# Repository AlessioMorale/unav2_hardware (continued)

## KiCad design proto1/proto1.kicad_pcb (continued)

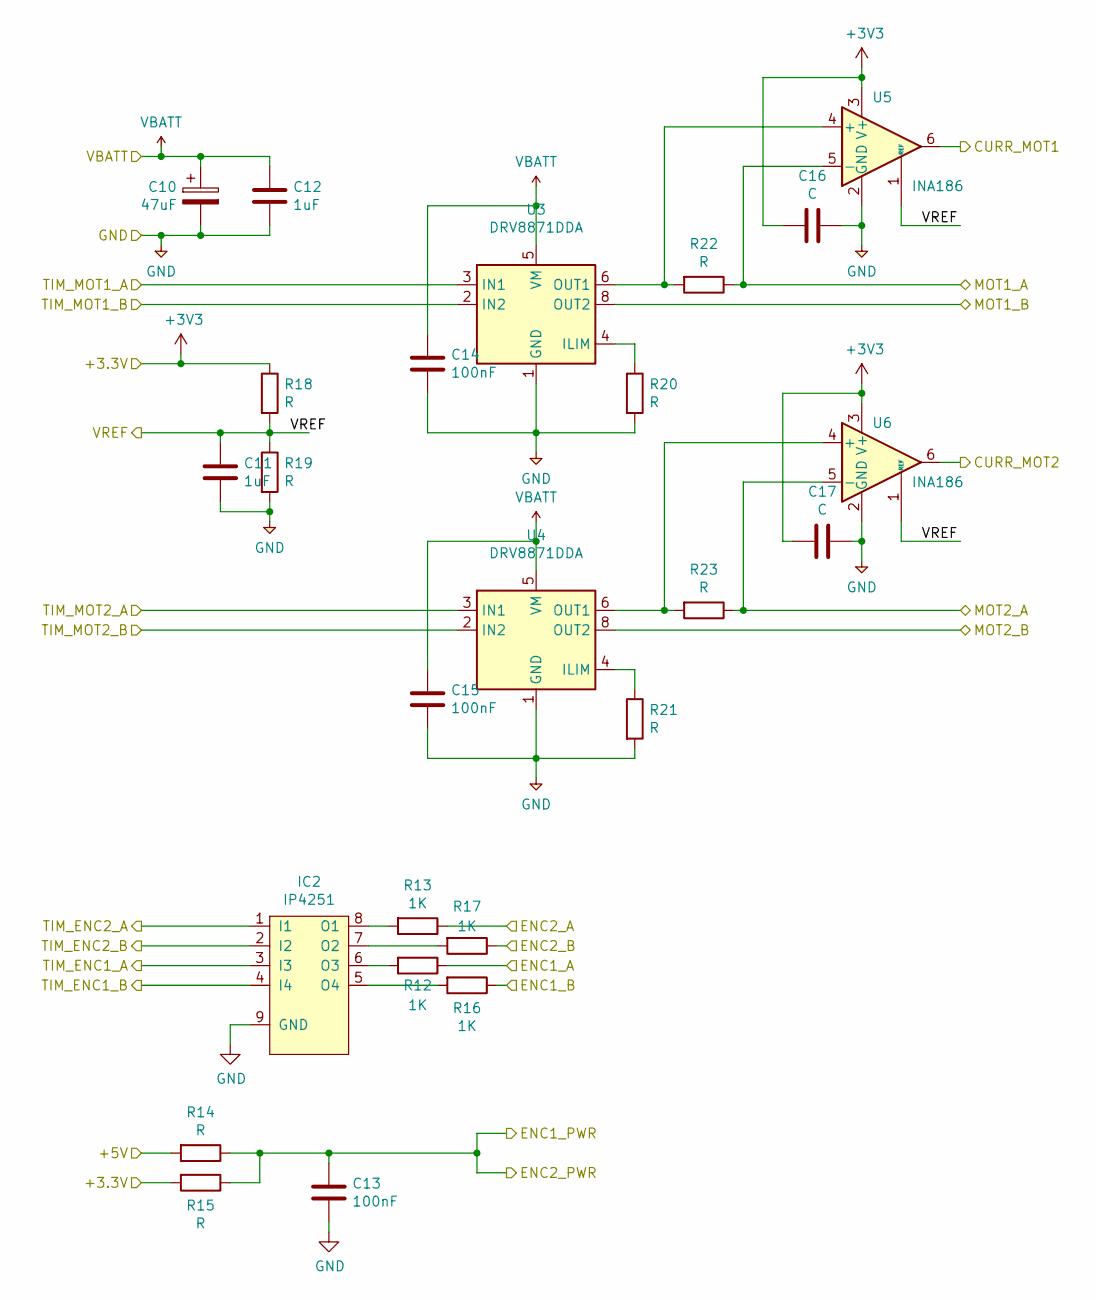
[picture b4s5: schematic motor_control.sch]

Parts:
C10: 47uF; CP_Elec_6.3x5.8
C11: 1uF; C_0402_1005Metric
C12: 1uF; C_0805_2012Metric
C13, C14, C15: 100nF; C_0603_1608Metric
C16, C17: C; C_0402_1005Metric
IC2: IP4251; HUSON8; Digikey 1727-5678-1-ND
R12, R13, R16, R17: 1K; R_0402_1005Metric
R14, R15, R18, R19, R20, R21: R; R_0402_1005Metric
R22, R23: R; R_0805_2012Metric
U3, U4: DRV8871DDA; Texas_HTSOP-8-1EP_3.9x4.9mm_P1.27mm_EP2.95x4.9mm_Mask2.4x3.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
U5, U6: INA186; SOT-23-6

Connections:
+3V3: C16.2, C17.2, R15.2, R18.1, U5.3 (V+), U6.3 (V+); also elsewhere on the board
+5V: R14.2; also elsewhere on the board
+BATT: C10.1, C12.1, C14.1, C15.1, U3.5 (VM), U4.5 (VM); also elsewhere on the board
/Motor control/ENC1_A: R12.1; also elsewhere on the board
/Motor control/ENC1_B: R16.1; also elsewhere on the board
/Motor control/ENC1_PWR: C13.1, R14.1, R15.1; also elsewhere on the board
/Motor control/ENC2_A: R13.1; also elsewhere on the board
/Motor control/ENC2_B: R17.1; also elsewhere on the board
/Motor control/MOT1_A: R22.1, U5.5 (-); also elsewhere on the board
/Motor control/MOT1_B: U3.8 (OUT2); also elsewhere on the board
/Motor control/MOT2_A: R23.1, U6.5 (-); also elsewhere on the board
/Motor control/MOT2_B: U4.8 (OUT2); also elsewhere on the board
/PC0: U5.6; also elsewhere on the board
/PC1: U6.6; also elsewhere on the board
/PC3: C11.1, R18.2, R19.1, U5.1 (REF), U6.1 (REF); also elsewhere on the board
/PC6: IC2.3 (I3); also elsewhere on the board
/PC7: IC2.4 (I4); also elsewhere on the board
/PD12: IC2.1 (I1); also elsewhere on the board
/PD13: IC2.2 (I2); also elsewhere on the board
/PE8: U3.2 (IN2); also elsewhere on the board
/PE9: U3.3 (IN1); also elsewhere on the board
/PE10: U4.2 (IN2); also elsewhere on the board
/PE11: U4.3 (IN1); also elsewhere on the board
GND: C10.2, C11.2, C12.2, C13.2, C14.2, C15.2, C16.1, C17.1, IC2.9 (GND), R19.2, R20.2, R21.2, U3.1 (GND), U3.7 (GND), U3.9 (GND), U4.1 (GND), U4.7 (GND), U4.9 (GND), U5.2 (GND), U6.2 (GND); also elsewhere on the board
unnamed: IC2.5 (O4), R16.2
unnamed: IC2.6 (O3), R12.2
unnamed: IC2.7 (O2), R17.2
unnamed: IC2.8 (O1), R13.2
unnamed: R20.1, U3.4 (ILIM)
unnamed: R21.1, U4.4 (ILIM)
unnamed: R22.2, U3.6 (OUT1), U5.4 (+)
unnamed: R23.2, U4.6 (OUT1), U6.4 (+)

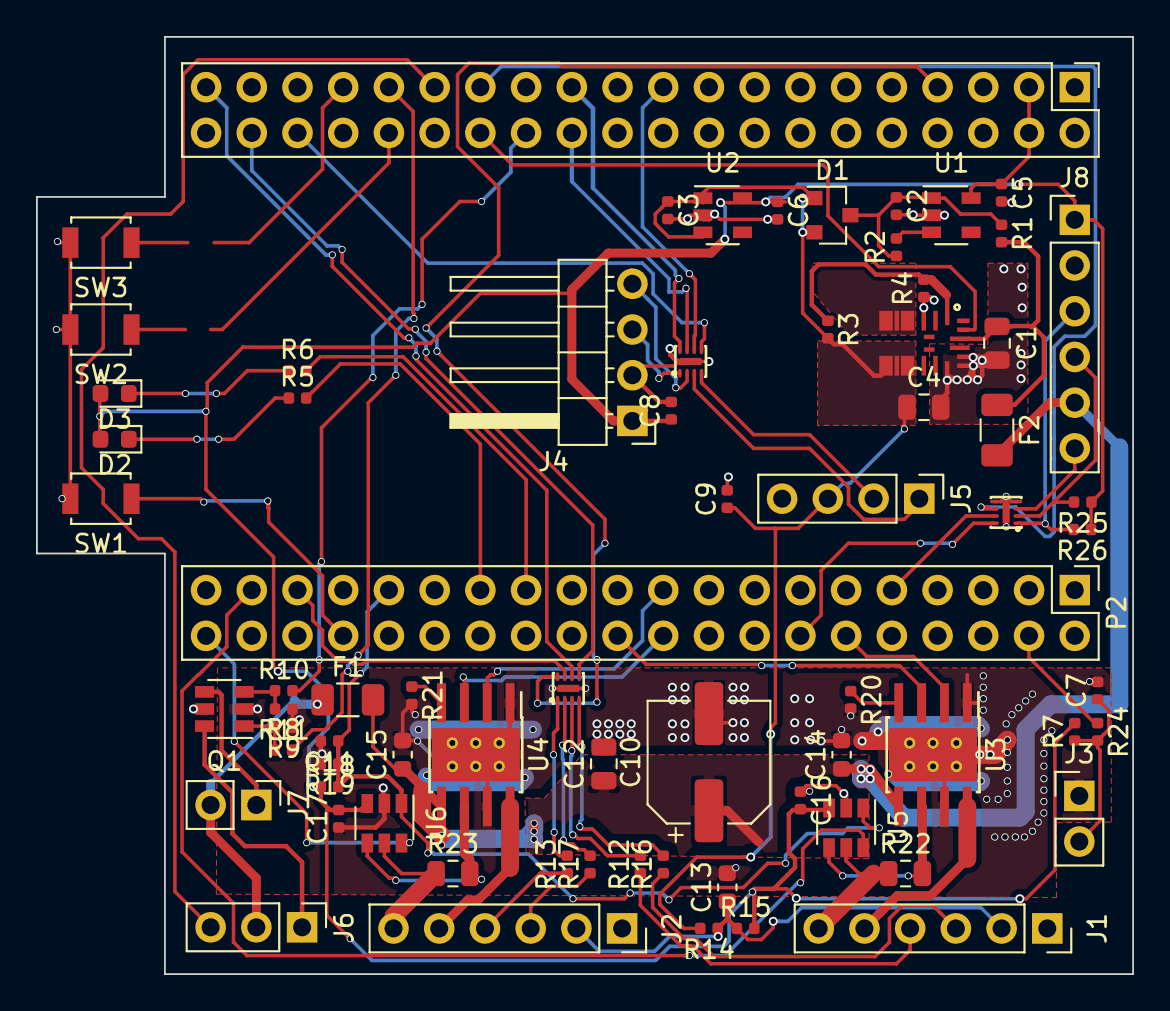
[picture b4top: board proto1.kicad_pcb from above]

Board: 2 copper layers, 60.9 x 52.1 mm, 72 parts (0 on the bottom side), 71 nets.

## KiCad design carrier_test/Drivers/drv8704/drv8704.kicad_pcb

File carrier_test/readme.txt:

Link to docs for the F4 board used:

doc
http://wiki.stm32duino.com/index.php?title=STM32F407

schematic
http://wiki.stm32duino.com/images/5/5c/STM32_F4VE_SCHEMATIC.PDF

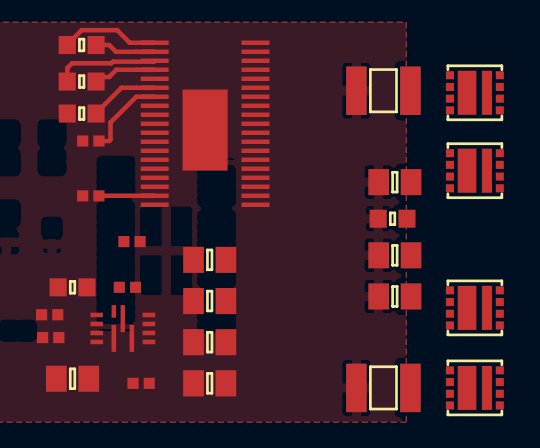
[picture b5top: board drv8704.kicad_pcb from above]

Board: 2 copper layers, 28 parts (0 on the bottom side), 29 nets.

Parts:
C1, C6, C7: 0.1μF; 0603
C2, C3, C5, C9, C13, C14, C15, C16: 22UF; 0805
C4: 0.1UF; 0402
C8, C10: 1UF; 0603
IC1: DRV8704; HTSSOP-38
IC2: MP8759; QFN-12_MPS_NB679
Q1, Q2, Q3, Q4: SiZ340DT; PowerPair-3x3
R1: 10K; 0402
R2, R3: 0.001; 1210
R4: 3.3; 0402
R5, R6: NC; 0402
R7: 41.2K; 0402
R8: 5.6K; 0402

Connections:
/Driver/A1: IC1.37, Q2.S1D2
/Driver/A2: IC1.30, Q4.S1D2
/Driver/B1: IC1.28, Q1.S1D2
/Driver/B2: IC1.21, Q3.S1D2
/Driver/BIN2: IC1.12, IC1.13
/Driver/FAULTn: IC1.18, R1.1
/Driver/VMOT: C1.1, C2.1, C3.1, C5.1, C8.2, IC1.4, Q1.D1, Q2.D1, Q3.D1, Q4.D1
/Power/VIN: C9.1, IC2.1
/Power/Vout: C13.2, C14.2, C15.2, C16.2, IC2.5, R7.1
GND: C1.2, C2.2, C3.2, C4.1, C5.2, C6.2, C10.2, C13.1, C14.1, C15.1, C16.1, IC1.5, IC1.19, IC1.24, IC1.33, IC1.38, IC1.39, IC2.2, IC2.10, R2.2, R3.2, R8.2
unnamed: C4.2, IC1.7
unnamed: C6.1, IC1.6
unnamed: C7.1, IC1.1
unnamed: C7.2, IC1.2
unnamed: C8.1, IC1.3
unnamed: C10.1, IC2.9
unnamed: IC2.7, R5.1, R5.2, R6.1
unnamed: IC1.22, Q3.G1
unnamed: IC1.23, Q3.G2
unnamed: IC1.25, Q1.S2, Q3.S2, R3.1
unnamed: IC1.26, Q1.G2
unnamed: IC1.27, Q1.G1
unnamed: IC1.31, Q4.G1
unnamed: IC1.32, Q4.G2
unnamed: IC1.34, Q2.S2, Q4.S2, R2.1
unnamed: IC1.35, Q2.G2
unnamed: IC1.36, Q2.G1
unnamed: IC2.8, R4.1
unnamed: IC2.11, R6.2, R7.2, R8.1

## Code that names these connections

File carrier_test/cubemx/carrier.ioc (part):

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Mcu.Name=STM32F407V(E-G)Tx
Mcu.Package=LQFP100
Mcu.UserName=STM32F407VETx
PA0-WKUP.GPIOParameters=GPIO_Label
PA0-WKUP.GPIO_Label=I_KEY_UP
PA0-WKUP.Mode=SYS_WakeUp0
PA0-WKUP.Signal=SYS_WKUP
PA1.GPIOParameters=GPIO_Label
PA1.GPIO_Label=TIM_ENC3_B
PA1.Signal=S_TIM2_CH2
PA10.Mode=Asynchronous
PA10.Signal=USART1_RX
PA11.Mode=Device_Only
PA11.Signal=USB_OTG_FS_DM
PA12.Mode=Device_Only
PA12.Signal=USB_OTG_FS_DP
PA13.Mode=Serial_Wire
PA13.Signal=SYS_JTMS-SWDIO
PA14.Mode=Serial_Wire
PA14.Signal=SYS_JTCK-SWCLK
PA2.GPIOParameters=GPIO_Label
PA2.GPIO_Label=ADC_TEMP
PA2.Signal=ADCx_IN2
PA3.Signal=ADCx_IN3
PA5.GPIOParameters=GPIO_Label
PA5.GPIO_Label=TIM_ENC3_A
PA5.Signal=S_TIM2_CH1_ETR
PA6.GPIOParameters=GPIO_Label
PA6.GPIO_Label=O_LED1
PA6.Signal=GPIO_Output
PA7.GPIOParameters=GPIO_Label
PA7.GPIO_Label=O_LED2
PA7.Signal=GPIO_Output
PA9.Mode=Asynchronous
PA9.Signal=USART1_TX
PB0.GPIOParameters=GPIO_Label
PB0.GPIO_Label=O_FLASH_CS
PB0.Signal=GPIO_Output
PB1.GPIOParameters=GPIO_Label
PB1.GPIO_Label=O_SPI_CS2
PB1.Signal=GPIO_Output
PB10.Mode=Asynchronous
PB10.Signal=USART3_TX
PB11.Mode=Asynchronous
PB11.Signal=USART3_RX
PB12.GPIOParameters=GPIO_Label
PB12.GPIO_Label=I_MOT_FAULT1
PB12.Signal=GPXTI12
PB13.GPIOParameters=GPIO_Label
PB13.GPIO_Label=I_MOT_FAULT2
PB13.Signal=GPIO_Input
PB14.GPIOParameters=GPIO_Label
PB14.GPIO_Label=I_MOT_FAULT3
PB14.Signal=GPIO_Input
PB15.GPIOParameters=GPIO_Label
PB15.GPIO_Label=TIM_AUX2_PWM
PB15.Signal=S_TIM12_CH2
PB3.Mode=Full_Duplex_Master
PB3.Signal=SPI1_SCK
PB4.Mode=Full_Duplex_Master
PB4.Signal=SPI1_MISO
PB5.Mode=Full_Duplex_Master
PB5.Signal=SPI1_MOSI
PB6.Mode=I2C
PB6.Signal=I2C1_SCL
PB7.Mode=I2C
PB7.Signal=I2C1_SDA
PB8.GPIOParameters=GPIO_Label
PB8.GPIO_Label=O_PWR_EN
PB8.Signal=GPIO_Output
PB9.GPIOParameters=GPIO_Label
PB9.GPIO_Label=TIM_AUX_PWM
PB9.Signal=S_TIM11_CH1
PC0.GPIOParameters=GPIO_Label
PC0.GPIO_Label=ADC_MOT1_CUR
PC0.Signal=ADCx_IN10
PC1.GPIOParameters=GPIO_Label
PC1.GPIO_Label=ADC_MOT2_CUR
PC1.Signal=ADCx_IN11
PC10.Mode=mmc_4_bits_Wide_bus
PC10.Signal=SDIO_D2
PC11.Mode=mmc_4_bits_Wide_bus
PC11.Signal=SDIO_D3
PC12.Mode=mmc_4_bits_Wide_bus
PC12.Signal=SDIO_CK
PC13-ANTI_TAMP.GPIOParameters=GPIO_Label
PC13-ANTI_TAMP.GPIO_Label=I_FAN_INDEX
PC13-ANTI_TAMP.Signal=GPIO_Input
PC14-OSC32_IN.Mode=LSE-External-Oscillator
PC14-OSC32_IN.Signal=RCC_OSC32_IN
PC15-OSC32_OUT.Mode=LSE-External-Oscillator
PC15-OSC32_OUT.Signal=RCC_OSC32_OUT
PC2.GPIOParameters=GPIO_Label
PC2.GPIO_Label=ADC_MOT3_CUR
PC2.Signal=ADCx_IN12
PC3.Signal=ADCx_IN13
PC4.GPIOParameters=GPIO_Label
PC4.GPIO_Label=ADC_BATT_CUR
PC4.Signal=ADCx_IN14
PC5.GPIOParameters=GPIO_Label
PC5.GPIO_Label=ADC_BATT_VOL
PC5.Signal=ADCx_IN15
PC6.GPIOParameters=GPIO_Label
PC6.GPIO_Label=TIM_ENC1_A
PC6.Signal=S_TIM3_CH1
PC7.GPIOParameters=GPIO_Label
PC7.GPIO_Label=TIM_ENC1_B
PC7.Signal=S_TIM3_CH2
PC8.Mode=mmc_4_bits_Wide_bus
PC8.Signal=SDIO_D0
PC9.Mode=mmc_4_bits_Wide_bus
PC9.Signal=SDIO_D1
PD10.GPIOParameters=GPIO_Label
PD10.GPIO_Label=IO_AUX2
PD10.Signal=GPIO_Input
PD11.GPIOParameters=GPIO_Label
PD11.GPIO_Label=IO_AUX1
PD11.Signal=GPIO_Output
PD12.GPIOParameters=GPIO_Label
PD12.GPIO_Label=TIM_ENC2_A
PD12.Signal=S_TIM4_CH1
PD13.GPIOParameters=GPIO_Label
PD13.GPIO_Label=TIM_ENC2_B
PD13.Signal=S_TIM4_CH2
PD2.Mode=mmc_4_bits_Wide_bus
PD2.Signal=SDIO_CMD
PD5.Mode=Asynchronous
PD5.Signal=USART2_TX
PD6.Mode=Asynchronous
PD6.Signal=USART2_RX
PE0.GPIOParameters=GPIO_Label
PE0.GPIO_Label=O_PWR_MOT_EN
PE0.Signal=GPIO_Output
PE1.GPIOParameters=GPIO_Label
PE1.GPIO_Label=O_PWR_SBC_EN
PE1.Signal=GPIO_Output
PE10.GPIOParameters=GPIO_Label
PE10.GPIO_Label=TIM_MOT2_B
PE10.Mode=Output Compare2 CH2 CH2N
PE10.Signal=TIM1_CH2N
PE11.GPIOParameters=GPIO_Label
PE11.GPIO_Label=TIM_MOT2_A
PE11.Signal=S_TIM1_CH2
PE12.GPIOParameters=GPIO_Label
PE12.GPIO_Label=TIM_MOT3_B
PE12.Mode=Output Compare3 CH3 CH3N
PE12.Signal=TIM1_CH3N
PE13.GPIOParameters=GPIO_Label
PE13.GPIO_Label=TIM_MOT3_A
PE13.Signal=S_TIM1_CH3
PE14.GPIOParameters=GPIO_Label
PE14.GPIO_Label=O_MOT_ENABLE
PE14.Signal=GPIO_Output
PE15.Mode=Activate-Break-Input
PE15.Signal=TIM1_BKIN
PE3.GPIOParameters=GPIO_Label
PE3.GPIO_Label=I_KEY1
PE3.Signal=GPIO_Input
PE4.GPIOParameters=GPIO_Label
PE4.GPIO_Label=I_KEY0
PE4.Signal=GPIO_Input
PE5.GPIOParameters=GPIO_Label
PE5.GPIO_Label=TIM_FAN_PWM
PE5.Signal=S_TIM9_CH1
PE6.GPIOParameters=GPIO_Label
PE6.GPIO_Label=TIM_AUX3_PWM
PE6.Signal=GPIO_Input
PE7.GPIOParameters=GPIO_Label
PE7.GPIO_Label=O_SPI_CS3
PE7.Signal=GPIO_Output
PE8.GPIOParameters=GPIO_Label
PE8.GPIO_Label=TIM_MOT1_B
PE8.Mode=Output Compare1 CH1 CH1N
PE8.Signal=TIM1_CH1N
PE9.GPIOParameters=GPIO_Label
PE9.GPIO_Label=TIM_MOT1_A
PE9.Signal=S_TIM1_CH1
PH0-OSC_IN.Mode=HSE-External-Oscillator
PH0-OSC_IN.Signal=RCC_OSC_IN
PH1-OSC_OUT.Mode=HSE-External-Oscillator
PH1-OSC_OUT.Signal=RCC_OSC_OUT
RCC.HSE_VALUE=8000000
RCC.SYSCLKFreq_VALUE=72000000
RCC.SYSCLKSource=RCC_SYSCLKSOURCE_PLLCLK
board=custom

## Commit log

2018-06-05 Initial commit for carrier prototype
2018-07-11 [CUBEMX] - initial config.
2018-07-12 Add readme with links to doc
2018-07-12 Update CubeMX doc
2018-07-12 updated schematic
2018-07-12 update CubeMX config
2018-07-15 update schematic
2018-07-16 Fix supply, add gps/imu serial, oled
2018-07-17 Update CubeMX ioc
2018-07-19 Schematic update
2018-07-24 Driver drv8704
2018-07-26 driver/supply board
2018-12-17 [UNAV2] - initial design, standalone
2018-12-17 [UNAV2] - initial draft of drv8704 based driver
2018-12-17 [UNAV2]
2019-01-04 standalone version of unav2 based on stm32f405rgt
2019-12-30 rev 0
2020-01-05 Cleanup old designs
2020-01-05 test design of mcu+driver boards(do not build!! it is just less than an idea right now)
2020-01-05 Add integrated board design, to be used as an initial prototype to develop the fw
2020-01-05 add script to export to pdf, include pdf schematic
2020-01-05 Add supply inversion protection diode, move custom symbol to project lib
2020-01-07 Beta 1 (move fan tach pin to a timer input)
2020-01-07 update pdf schematic
2020-01-11 Update documentation
2020-01-25 Fix BOM
2020-01-25 Add interactive BOM export (via the awesome https://github.com/openscopeproject/InteractiveHtmlBom plugin)
2020-01-25 Link bom (via htmlpreview) to the README.md
2020-02-04 Fixes for #1, #3, #4 & #6
2020-06-04 Additional fixes
2020-08-10 V 0.3: - use a 6 pins connector for each motor - use vertical connectors for usb and serial - additional jst/sh for swt in the back of the board - additional stitching on ground plane
2020-08-10 V 0.3: update pdf, gerbers and rendering
2021-12-30 Backlink to CADLAB.io has been added.
